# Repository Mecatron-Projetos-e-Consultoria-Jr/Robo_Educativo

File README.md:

# Robo_Educativo(Lembrar de tirar essa parte)

# Instalação
- Preparando a IDE: A IDE do Arduino não possui nativamente as placas da espressif em seu banco de dados. Portanto, é necessário instalar a ESP. [Este artigo](https://www.usinainfo.com.br/blog/programar-esp32-com-a-ide-arduino-tutorial-completo/) ensina passo a passo o processo(Configuração do ESP32 na IDE do Arduino). 
- Para que a interface funcione, copie a biblioteca do Nextion, localizada em Programação/IHM 3,5/Biblioteca_Nextion_ESP, para a basta "libraries" criada localmente pela IDE.
- O arquivo da programação principal está em Programação/ESP32/src/main.cpp. 
- Antes de realizar o upload para o microcontrolador no arquivo main.cpp é preciso mudar as configurações da conexão wifi. Nas linhas 15 e 16 mude para o nome e senha de rede local, respectivamente.
- Depois de tudo configurado, faça o upload da programação para a ESP32.

-------------------------------------------------------------------------------------------------------------------

# Robô Educativo

## Project Overview 
Desenvolvimento de uma interface hibrida que permite a integração e utilização de sensores de três diferentes kits robóticos de aprendizagem: Kazi EV5, Engino, Fischer Technik. Composto por 3 shields, e um centro de controle com uma tela touch para interação homem-máquina.

### Tecnologias utilizadas

#### Controle 

|Tipo|Nome|
|----|----|
|Sensor|`Fischer`|
|Sensor|`Engino`|
|Sensor|`Kazi`|
|Sensor|`Grove`|
|Comunicação|`OTA`|
|Linguagem|`C++`|

#### Eletrônica 

|Tipo|Nome|
|----|----|
|Controlador|`ESP32`|

#### Software

|Tipo|Nome|
|----|----|
|Interface|`Nextion Touch Screen`|

## Detalhes

### Datas
- Início - 020
- Fim - 021
### Membros Executores 
- Crotti (saiu na metade do projeto)- `ECA019`;
- Erik - `ECA019`;
- Natália - `ECA020`.

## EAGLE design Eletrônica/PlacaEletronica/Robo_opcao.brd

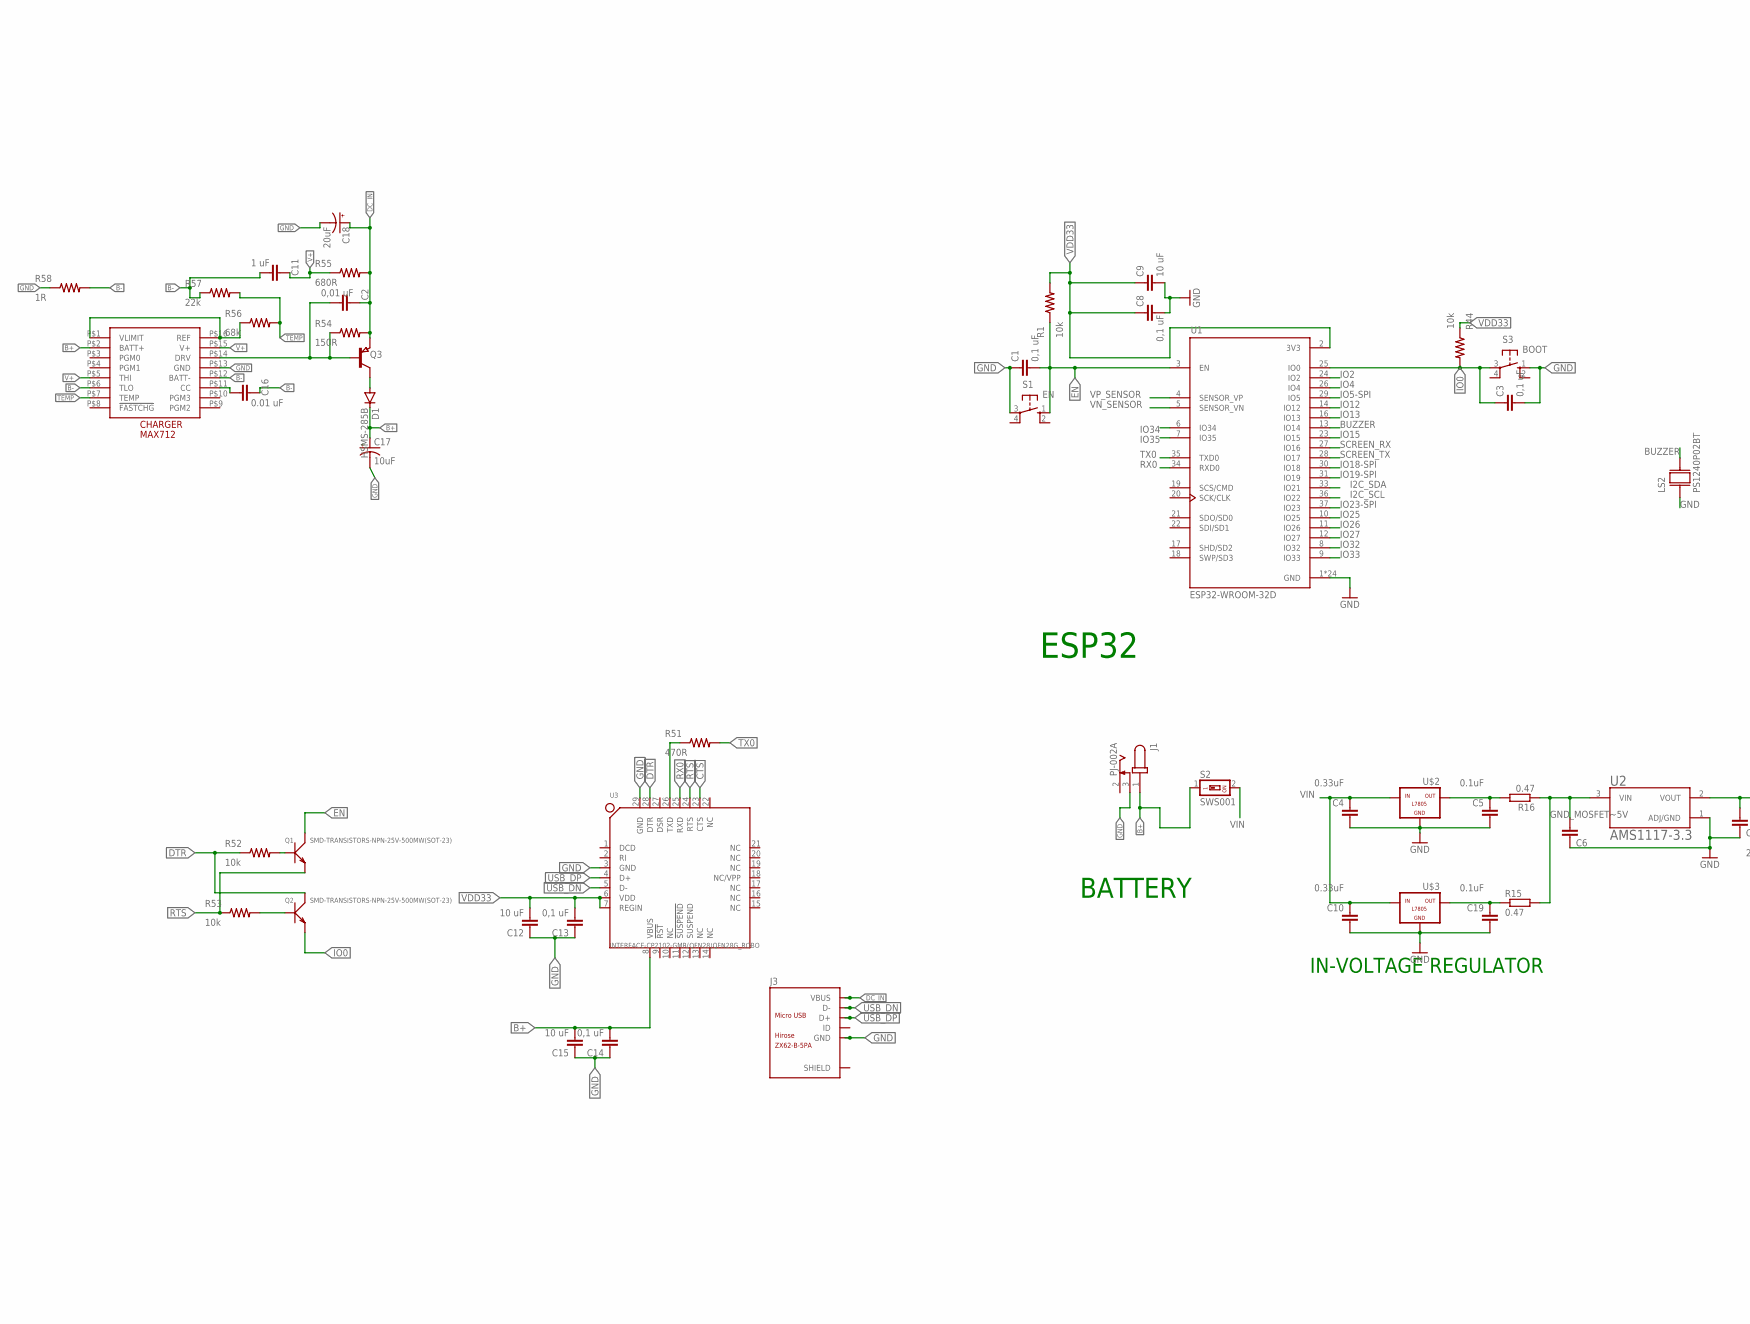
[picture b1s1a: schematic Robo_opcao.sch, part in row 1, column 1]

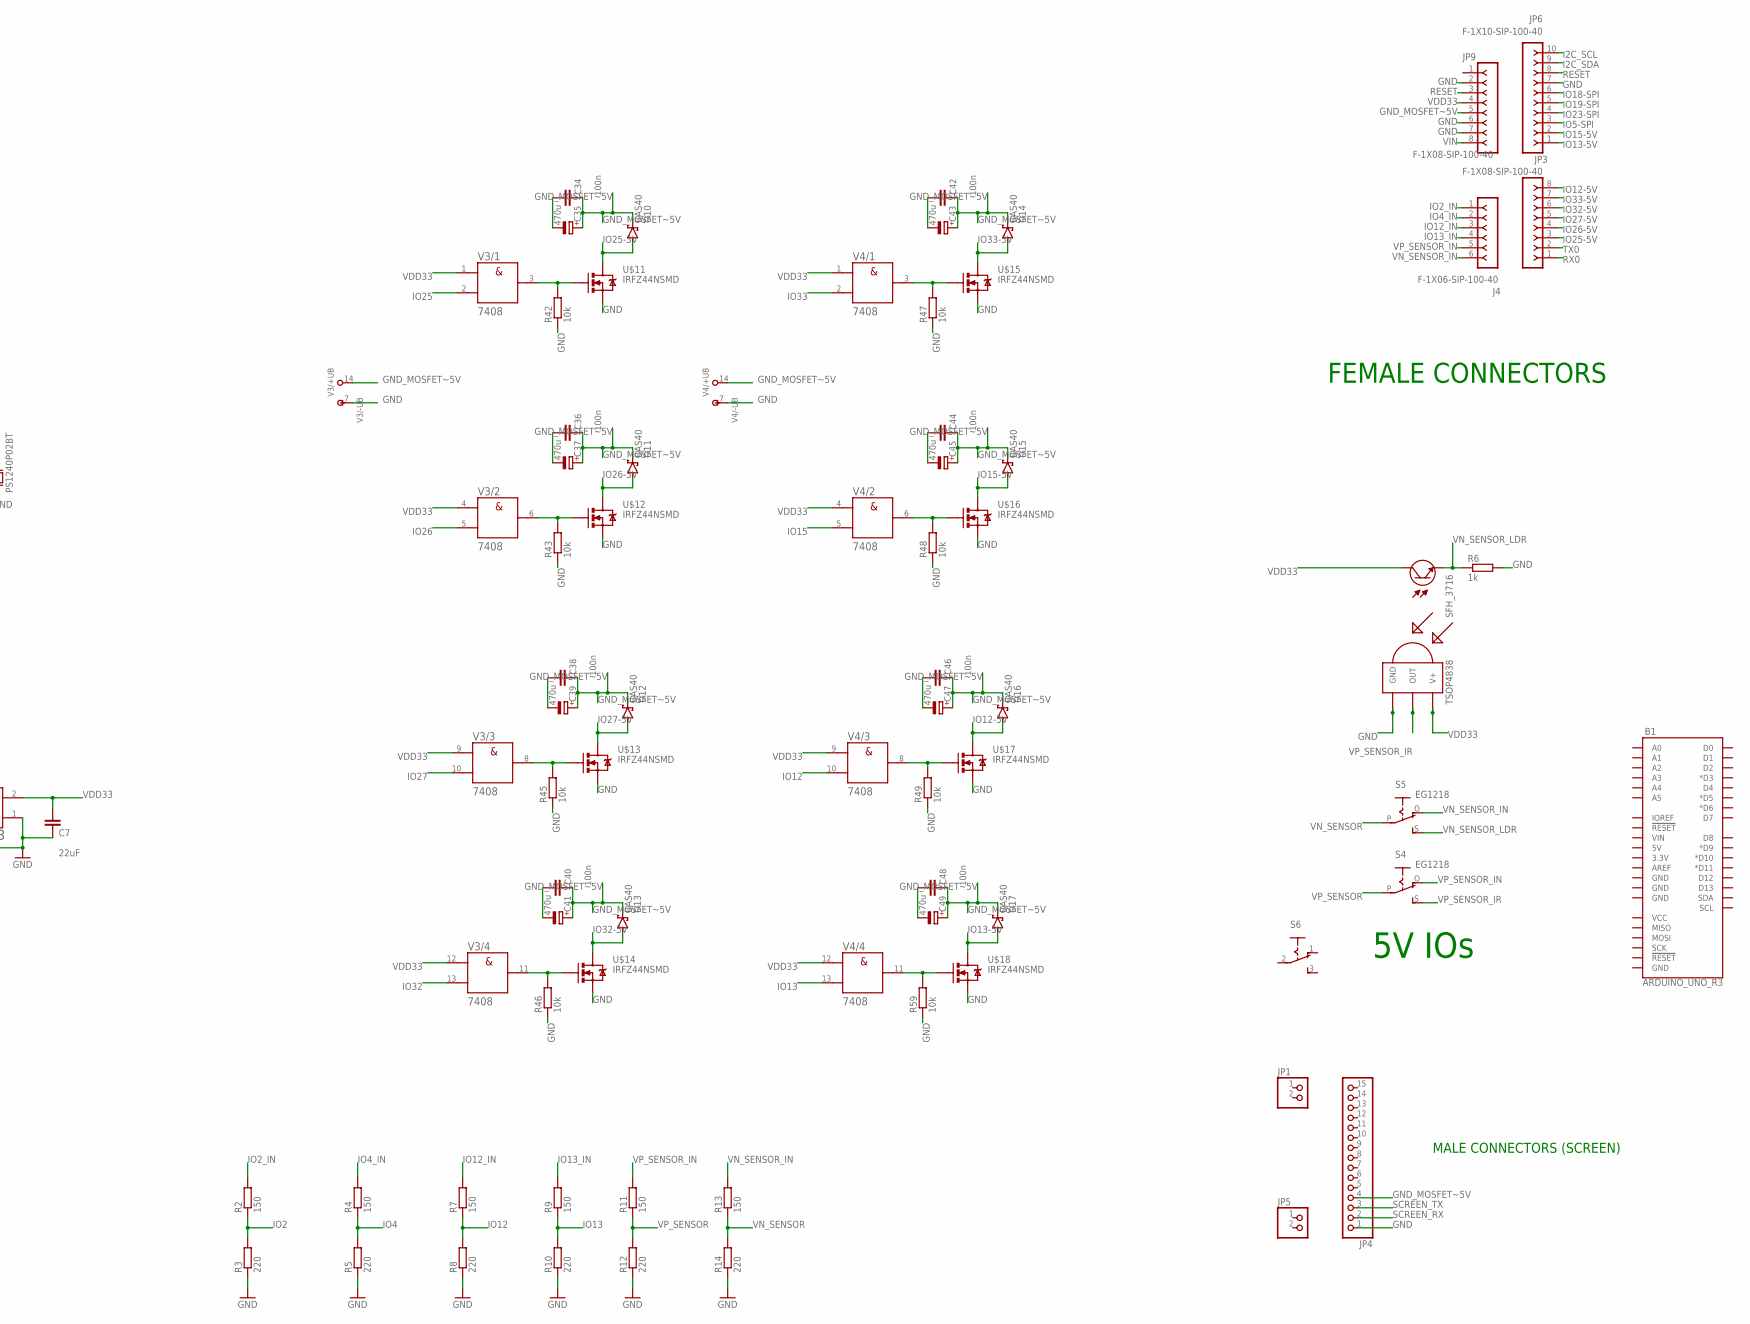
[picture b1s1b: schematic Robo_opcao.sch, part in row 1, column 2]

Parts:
B1: ARDUINO_UNO_R3; ARDUINO_R3
C1, C3, C8, C13, C14: 0,1 uF; C0603
C2: 0,01 uF; C0603
C4, C10: 0.33uF; 0402
C5, C6, C19: 0.1uF; 0402
C7: 22uF; 0402
C9, C12, C15: 10 uF; C0603
C11: 1 uF; C0603
C16: 0.01 uF; C0603
C17: 10uF; 0402_POL
C18: 20uF; 0402_POL
C34, C36, C38, C40, C42, C44, C46, C48: 100n; 0402
C35, C37, C39, C41, C43, C45, C47, C49: 470u; 150CLZ-0810
CHARGER: MAX712; DIP14
D1: HSMS-285B; SOT323
D10, D11, D12, D13, D14, D15, D16, D17: BAS40; SOT23
J1: PJ-002A; CUI_PJ-002A
J3: ZX62-B-5PA; ZX62-B-5PA(11)
J4: F-1X06-SIP-100-40; SIP-100-06-40
JP1, JP5: PINHD-1X2_2.54-SMD; 1X02SMD
JP3, JP9: F-1X08-SIP-100-40; SIP-100-08-40
JP4: PINHD-1X15_2.54-SMD; 1X15SMD
JP6: F-1X10-SIP-100-40; SIP-100-10-40
LS2: PS1240P02BT; XDCR_PS1240P02BT
Q1, Q2: SMD-TRANSISTORS-NPN-25V-500MW(SOT-23); SOT-23
Q3: PNP-TRANSISTOR_SOT23; SOT23
Q4: SFH_3716; TRANS_SFH_3716
Q5: TSOP4838; TSOP18XX
R1, R44, R52, R53: 10k; 0402
R2, R4, R7, R9, R11, R13: 150; M0805
R3, R5, R8, R10, R12, R14: 220; M0805
R6: 1k; M0805
R15, R16: 0.47; M0805
R42, R43, R45, R46, R47, R48, R49, R59: 10k; M0805
R51: 470R; 0402
R54: 150R; 0402
R55: 680R; 0402
R56: 68k; 0402
R57: 22k; 0402
R58: 1R; 0402
S1: EN; B3F-10XX
S2: SWS001; SMS-001
S3: BOOT; B3F-10XX
S4, S5: EG1218; EG1218_ROBO
S6: 255SB
U1: ESP32-WROOM-32D; MODULE_ESP32-WROOM-32D
U2: AMS1117-3.3; SOT229P700X180-4N
U3: INTERFACE-CP2102-GMR(QFN28)QFN28G_ROBO; QFN28G_0.5-5X5MM_ROBO
U$2, U$3: -L7805; L7805
U$11, U$12, U$13, U$14, U$15, U$16, U$17, U$18: IRFZ44NSMD; SMD
V3, V4: 7408; DIL14_FT

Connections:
B+: C14.2, C15.2, C17.P+ (+), CHARGER.P$2 (BATT+), D1.3 (C), J1.1, S2.1, U3.8 (VBUS)
B-: C11.2, C16.1, CHARGER.P$6 (TLO), CHARGER.P$12 (BATT-), R57.1, R58.2
BUZZER: LS2.2, U1.13 (IO14)
CTS: U3.23 (CTS)
DC_IN: C2.1, C18.P+ (+), J3.1 (VBUS), Q3.2 (E), R54.2, R55.2
DTR: Q2.3 (C), R52.1, U3.28 (DTR)
EN: C1.2, Q1.3 (C), R1.1, S1.1 (S), U1.3 (EN)
GND: C1.1, C3.2, C4.1, C5.1, C6.2, C7.2, C8.2, C9.2, C10.1, C12.1, C13.1, C14.1, C15.1, C17.P- (-), C18.P- (-), C19.1, CHARGER.P$13 (GND), J1.3, J3.5 (GND), JP4.1, JP6.7, JP9.2, JP9.6, JP9.7, LS2.1, Q5.GND, R3.1, R5.1, R6.2, R8.1, R10.1, R12.1, R14.1, R42.1, R43.1, R45.1, R46.1, R47.1, R48.1, R49.1, R58.1, R59.1, S1.3, S3.1 (S), U1.1 (GND), U1.15 (GND), U1.38 (GND), U1.39_1 (GND), U1.39_2 (GND), U1.39_3 (GND), U1.39_4 (GND), U1.39_5 (GND), U1.39_6 (GND), U1.39_7 (GND), U1.39_8 (GND), U1.39_9 (GND), U1.39_10 (GND), U1.39_11 (GND), U1.39_12 (GND), U1.39_13 (GND), U1.39_14 (GND), U1.39_15 (GND), U1.39_16 (GND), U1.39_17 (GND), U1.39_18 (GND), U1.39_19 (GND), U1.39_20 (GND), U1.39_21 (GND), U2.1 (ADJ/GND), U3.3 (GND), U3.29 (GND), U$2.GND, U$3.GND, U$11.3 (S), U$12.3 (S), U$13.3 (S), U$14.3 (S), U$15.3 (S), U$16.3 (S), U$17.3 (S), U$18.3 (S), V3.7 (-UB), V4.7 (-UB)
GND_MOSFET~5V: C6.1, C34.2, C35.+, C36.2, C37.+, C38.2, C39.+, C40.2, C41.+, C42.2, C43.+, C44.2, C45.+, C46.2, C47.+, C48.2, C49.+, D10.3 (C), D11.3 (C), D12.3 (C), D13.3 (C), D14.3 (C), D15.3 (C), D16.3 (C), D17.3 (C), JP4.4, JP9.5, R15.2, R16.1, U2.3 (VIN), V3.14 (+UB), V4.14 (+UB)
I2C_SCL: JP6.10, U1.36 (IO22)
I2C_SDA: JP6.9, U1.33 (IO21)
IO0: C3.1, Q2.2 (E), R44.2, S3.3, U1.25 (IO0)
IO2: R2.1, R3.2, U1.24 (IO2)
IO2_IN: J4.1, R2.2
IO4: R4.1, R5.2, U1.26 (IO4)
IO4_IN: J4.2, R4.2
IO5-SPI: JP6.3, U1.29 (IO5)
IO12: R7.1, R8.2, U1.14 (IO12), V4.10 (B)
IO12-5V: D16.1 (A), JP3.8, U$17.2 (D)
IO12_IN: J4.3, R7.2
IO13: R9.1, R10.2, U1.16 (IO13), V4.13 (B)
IO13-5V: D17.1 (A), JP6.1, U$18.2 (D)
IO13_IN: J4.4, R9.2
IO15: U1.23 (IO15), V4.5 (B)
IO15-5V: D15.1 (A), JP6.2, U$16.2 (D)
IO18-SPI: JP6.6, U1.30 (IO18)
IO19-SPI: JP6.5, U1.31 (IO19)
IO23-SPI: JP6.4, U1.37 (IO23)
IO25: U1.10 (IO25), V3.2 (B)
IO25-5V: D10.1 (A), JP3.3, U$11.2 (D)
IO26: U1.11 (IO26), V3.5 (B)
IO26-5V: D11.1 (A), JP3.4, U$12.2 (D)
IO27: U1.12 (IO27), V3.10 (B)
IO27-5V: D12.1 (A), JP3.5, U$13.2 (D)
IO32: U1.8 (IO32), V3.13 (B)
IO32-5V: D13.1 (A), JP3.6, U$14.2 (D)
IO33: U1.9 (IO33), V4.2 (B)
IO33-5V: D14.1 (A), JP3.7, U$15.2 (D)
IO34: U1.6 (IO34)
IO35: U1.7 (IO35)
unnamed: C19.2, R15.1, U$3.OUT
unnamed: C5.2, R16.2, U$2.OUT
unnamed: R51.1, U3.26 (TXD)
unnamed: C34.1, C35.-
unnamed: C36.1, C37.-
unnamed: Q1.1 (B), R52.2
unnamed: C38.1, C39.-
unnamed: C40.1, C41.-
unnamed: C42.1, C43.-
unnamed: C44.1, C45.-
unnamed: C46.1, C47.-
unnamed: C48.1, C49.-
unnamed: Q2.1 (B), R53.2
unnamed: C2.2, CHARGER.P$14 (DRV), Q3.1 (B), R54.1
unnamed: R42.2, U$11.1 (G), V3.3 (Y)
unnamed: D1.1 (A), Q3.3 (C)
unnamed: C16.2, CHARGER.P$11 (CC)
unnamed: CHARGER.P$1 (VLIMIT), CHARGER.P$16 (REF), R56.1
unnamed: R43.2, U$12.1 (G), V3.6 (Y)
unnamed: R45.2, U$13.1 (G), V3.8 (Y)
unnamed: R46.2, U$14.1 (G), V3.11 (Y)
unnamed: R47.2, U$15.1 (G), V4.3 (Y)
unnamed: R48.2, U$16.1 (G), V4.6 (Y)
unnamed: R49.2, U$17.1 (G), V4.8 (Y)
unnamed: R59.2, U$18.1 (G), V4.11 (Y)
RESET: JP6.8, JP9.3
RTS: Q1.2 (E), R53.1, U3.24 (RTS)
RX0: JP3.1, U1.34 (RXD0), U3.25 (RXD)
SCREEN_RX: JP4.2, U1.27 (IO16)
SCREEN_TX: JP4.3, U1.28 (IO17)
TEMP: CHARGER.P$7 (TEMP), R56.2, R57.2
TX0: JP3.2, R51.2, U1.35 (TXD0)
USB_DN: J3.2 (D-), U3.5 (D-)
USB_DP: J3.3 (D+), U3.4 (D+)
V+: C11.1, CHARGER.P$5 (THI), CHARGER.P$15 (V+), R55.1
VDD33: C7.1, C8.1, C9.1, C12.2, C13.2, JP9.4, Q4.1 (C), Q5.VCC (V+), R1.2, R44.1, U1.2 (3V3), U2.2 (VOUT), U3.6 (VDD), U3.7 (REGIN), V3.1 (A), V3.4 (A), V3.9 (A), V3.12 (A), V4.1 (A), V4.4 (A), V4.9 (A), V4.12 (A)
VIN: C4.2, C10.2, JP9.8, S2.2, U$2.IN, U$3.IN
VN_SENSOR: R13.1, R14.2, S5.P, U1.5 (SENSOR_VN)
VN_SENSOR_IN: J4.6, R13.2, S5.O
VN_SENSOR_LDR: Q4.2 (E), R6.1, S5.S
VP_SENSOR: R11.1, R12.2, S4.P, U1.4 (SENSOR_VP)
VP_SENSOR_IN: J4.5, R11.2, S4.O
VP_SENSOR_IR: Q5.OUT, S4.S

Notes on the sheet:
IN-VOLTAGE REGULATOR
FEMALE CONNECTORS
MALE CONNECTORS (SCREEN)
BATTERY
5V IOs
ESP32

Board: 2 copper layers, 116 parts (40 on the bottom side), 80 nets, no tracks yet.

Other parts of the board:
U$1: NEXTION

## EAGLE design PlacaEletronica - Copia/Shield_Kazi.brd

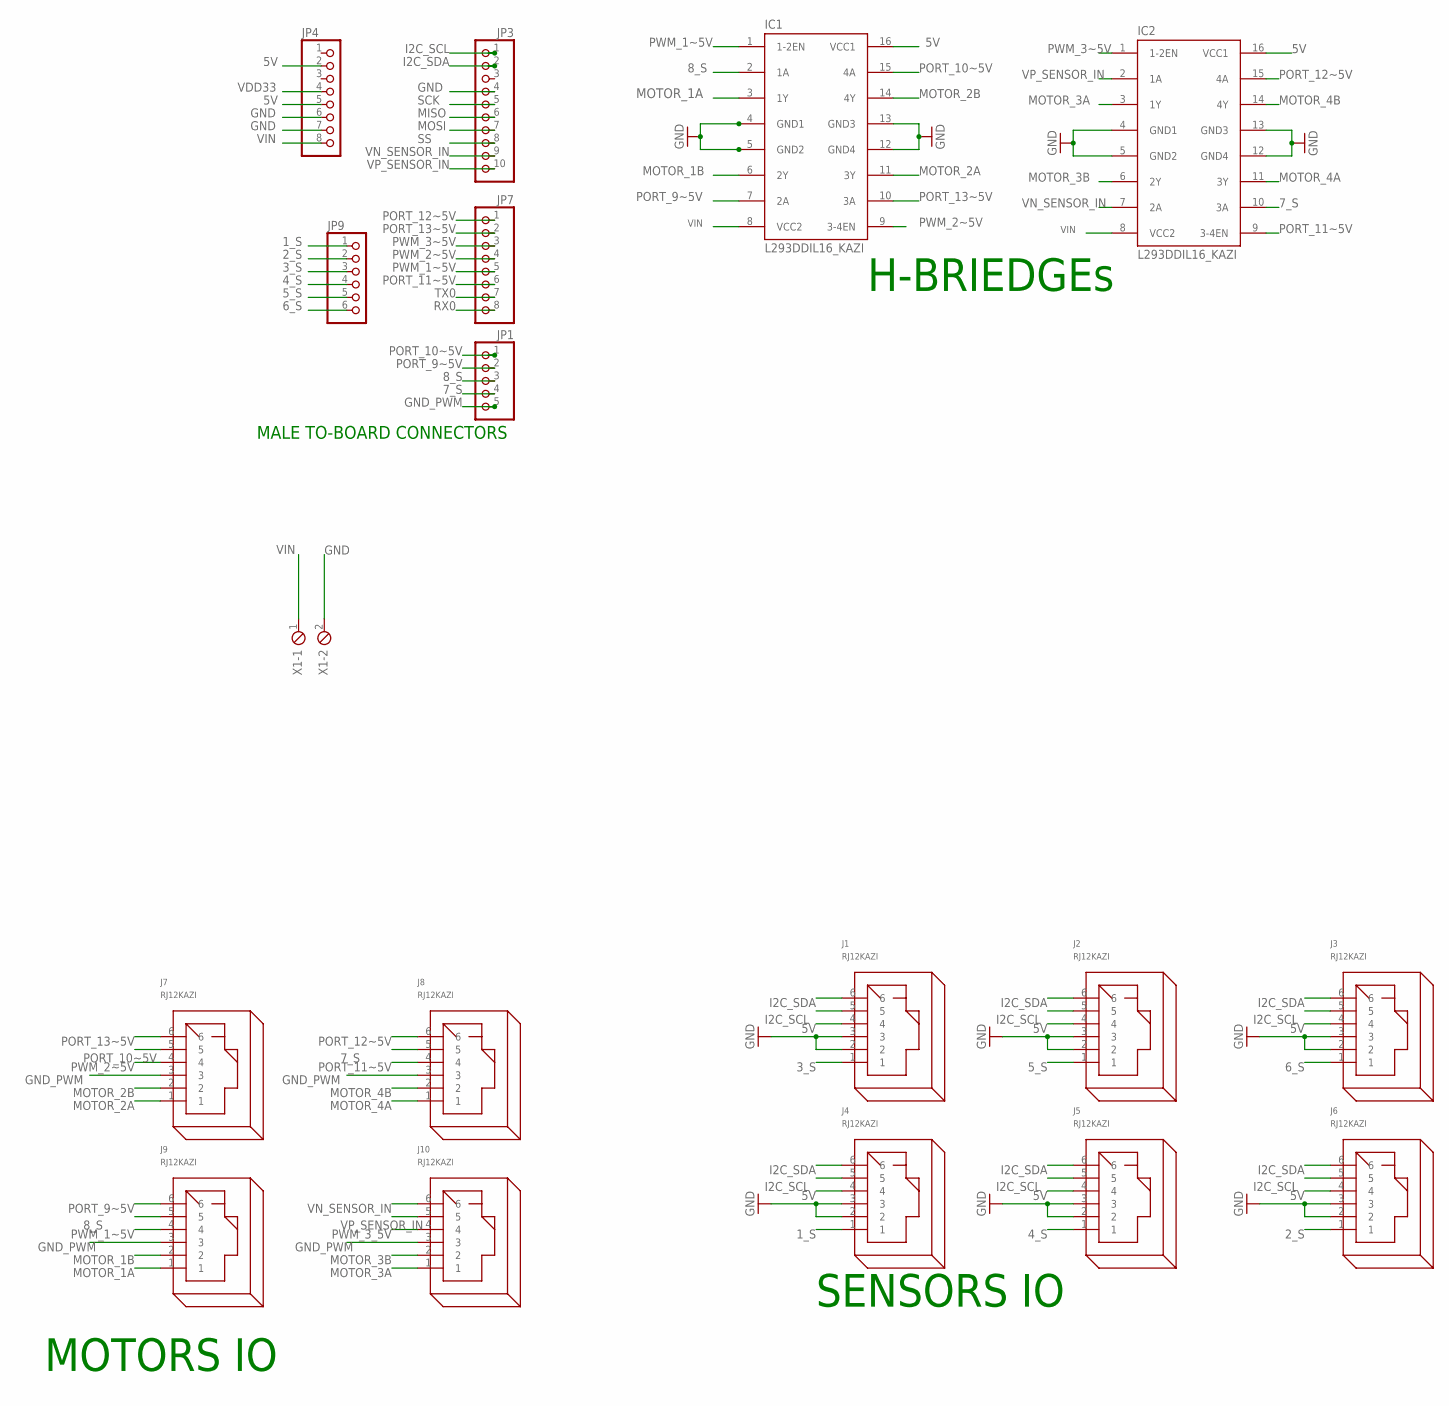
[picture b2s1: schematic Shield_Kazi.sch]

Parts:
IC1, IC2: L293DDIL16_KAZI; DIL16_KAZI
J1, J2, J3, J4, J5, J6, J7, J8, J9, J10: RJ12KAZI; RJ12_KAZI
JP1: PINHD-1X5_2.54-SMD; 1X05SMD
JP3: PINHD-1X10_2.54-SMD; 1X10SMD
JP4, JP7: PINHD-1X8_2.54-SMD; 1X08SMD
JP9: PINHD-1X6_2.54-SMD; 1X06SMD
X1: MPT21.3; 2POL254_1.3

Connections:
1_S: J4.1, JP9.1
2_S: J6.1, JP9.2
3_S: J1.1, JP9.3
4_S: J5.1, JP9.4
5V: IC1.16 (VCC1), IC2.16 (VCC1), J1.4, J2.4, J3.4, J4.4, J5.4, J6.4, JP4.2, JP4.5
5_S: J2.1, JP9.5
6_S: J3.1, JP9.6
7_S: IC2.10 (3A), J8.5, JP1.4
8_S: IC1.2 (1A), J9.5, JP1.3
GND: IC1.4 (GND1), IC1.5 (GND2), IC1.12 (GND4), IC1.13 (GND3), IC2.4 (GND1), IC2.5 (GND2), IC2.12 (GND4), IC2.13 (GND3), J1.2, J1.3, J2.2, J2.3, J3.2, J3.3, J4.2, J4.3, J5.2, J5.3, J6.2, J6.3, JP3.4, JP4.6, JP4.7, X1.2
GND_PWM: J7.3, J8.3, J9.3, J10.3, JP1.5
I2C_SCL: J1.5, J2.5, J3.5, J4.5, J5.5, J6.5, JP3.1
I2C_SDA: J1.6, J2.6, J3.6, J4.6, J5.6, J6.6, JP3.2
MISO: JP3.6
MOSI: JP3.7
MOTOR_1A: IC1.3 (1Y), J9.1
MOTOR_1B: IC1.6 (2Y), J9.2
MOTOR_2A: IC1.11 (3Y), J7.1
MOTOR_2B: IC1.14 (4Y), J7.2
MOTOR_3A: IC2.3 (1Y), J10.1
MOTOR_3B: IC2.6 (2Y), J10.2
MOTOR_4A: IC2.11 (3Y), J8.1
MOTOR_4B: IC2.14 (4Y), J8.2
PORT_9~5V: IC1.7 (2A), J9.6, JP1.2
PORT_10~5V: IC1.15 (4A), J7.5, JP1.1
PORT_11~5V: IC2.9 (3-4EN), J8.4, JP7.6
PORT_12~5V: IC2.15 (4A), J8.6, JP7.1
PORT_13~5V: IC1.10 (3A), J7.6, JP7.2
PWM_1~5V: IC1.1 (1-2EN), J9.4, JP7.5
PWM_2~5V: IC1.9 (3-4EN), J7.4, JP7.4
PWM_3_5V: J10.4
PWM_3~5V: IC2.1 (1-2EN), JP7.3
RX0: JP7.8
SCK: JP3.5
SS: JP3.8
TX0: JP7.7
VDD33: JP4.4
VIN: IC1.8 (VCC2), IC2.8 (VCC2), JP4.8, X1.1
VN_SENSOR_IN: IC2.7 (2A), J10.6, JP3.9
VP_SENSOR_IN: IC2.2 (1A), J10.5, JP3.10

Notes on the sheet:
MALE TO-BOARD CONNECTORS
H-BRIEDGEs
SENSORS IO
MOTORS IO

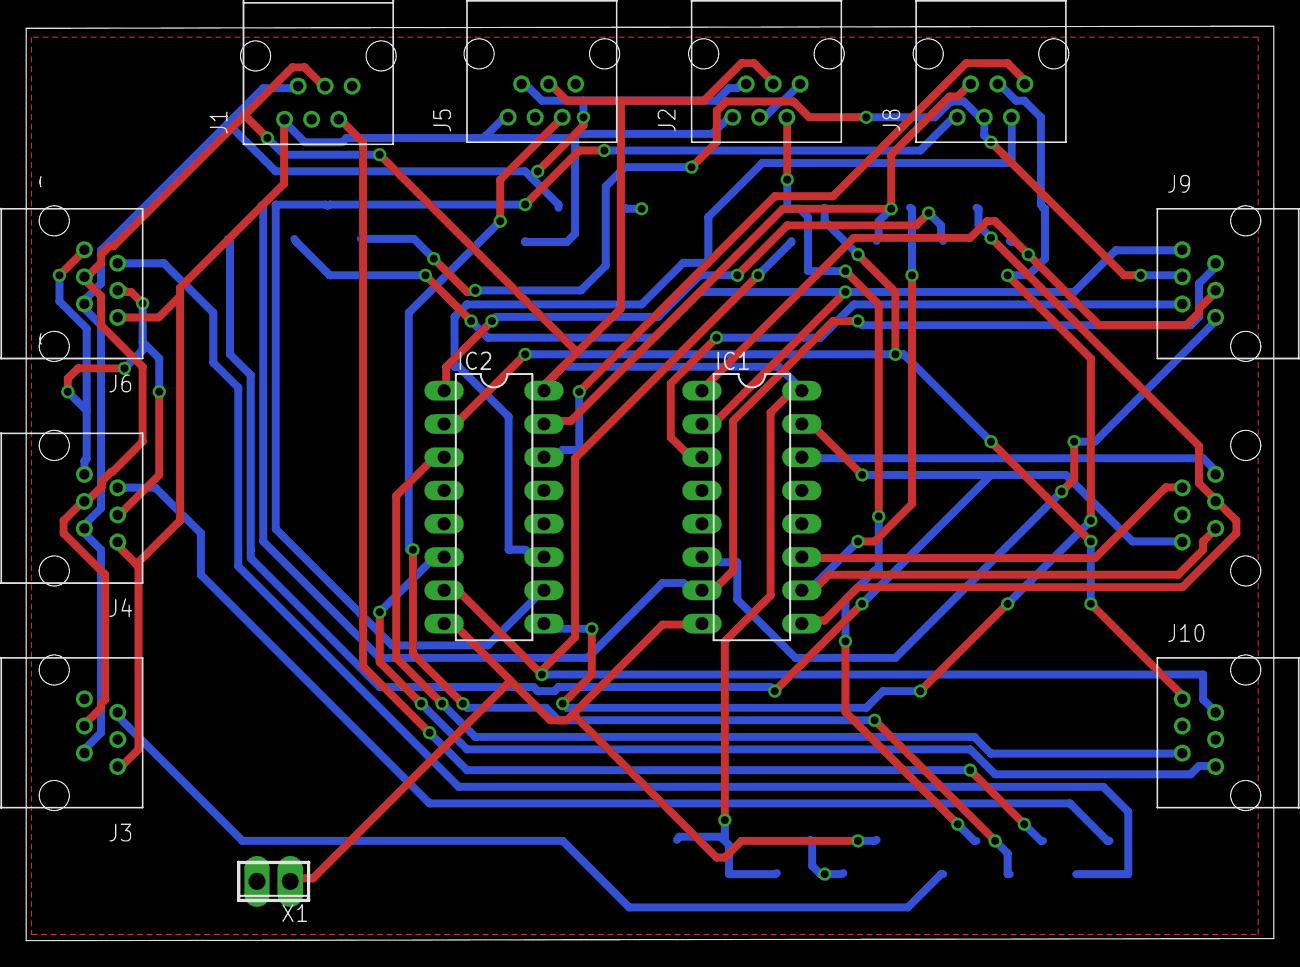
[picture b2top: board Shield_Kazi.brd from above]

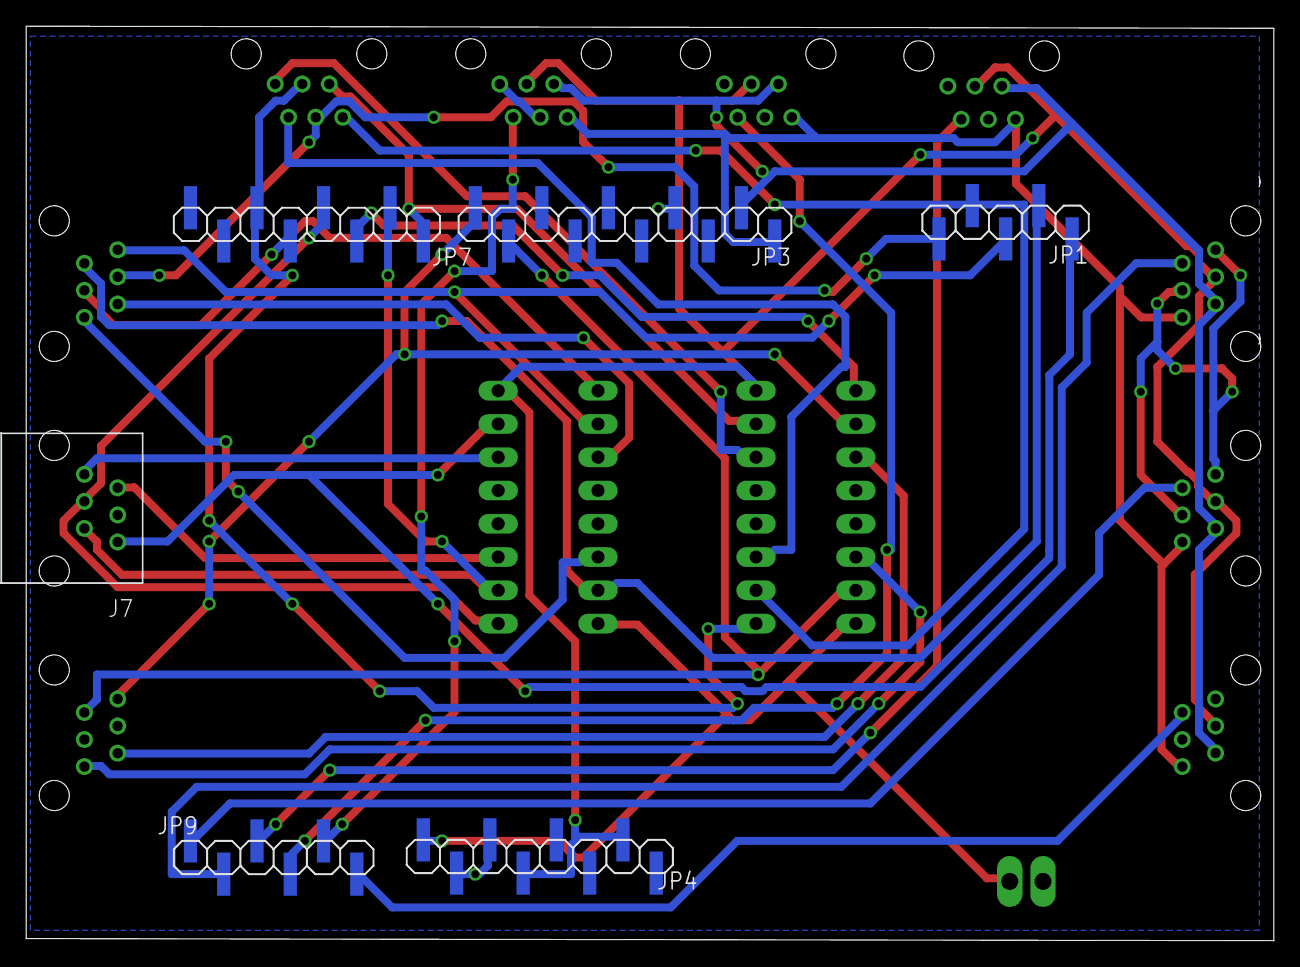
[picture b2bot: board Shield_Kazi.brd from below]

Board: 2 copper layers, 95.2 x 69.8 mm, 18 parts (6 on the bottom side), 32 nets.

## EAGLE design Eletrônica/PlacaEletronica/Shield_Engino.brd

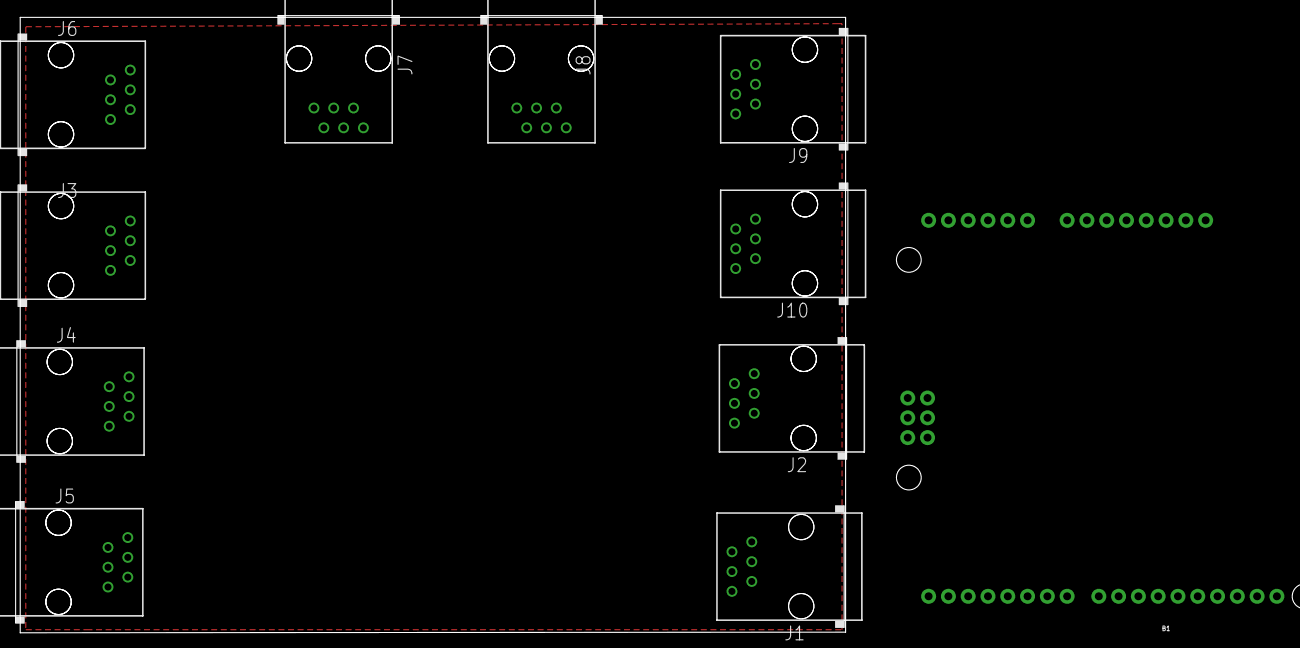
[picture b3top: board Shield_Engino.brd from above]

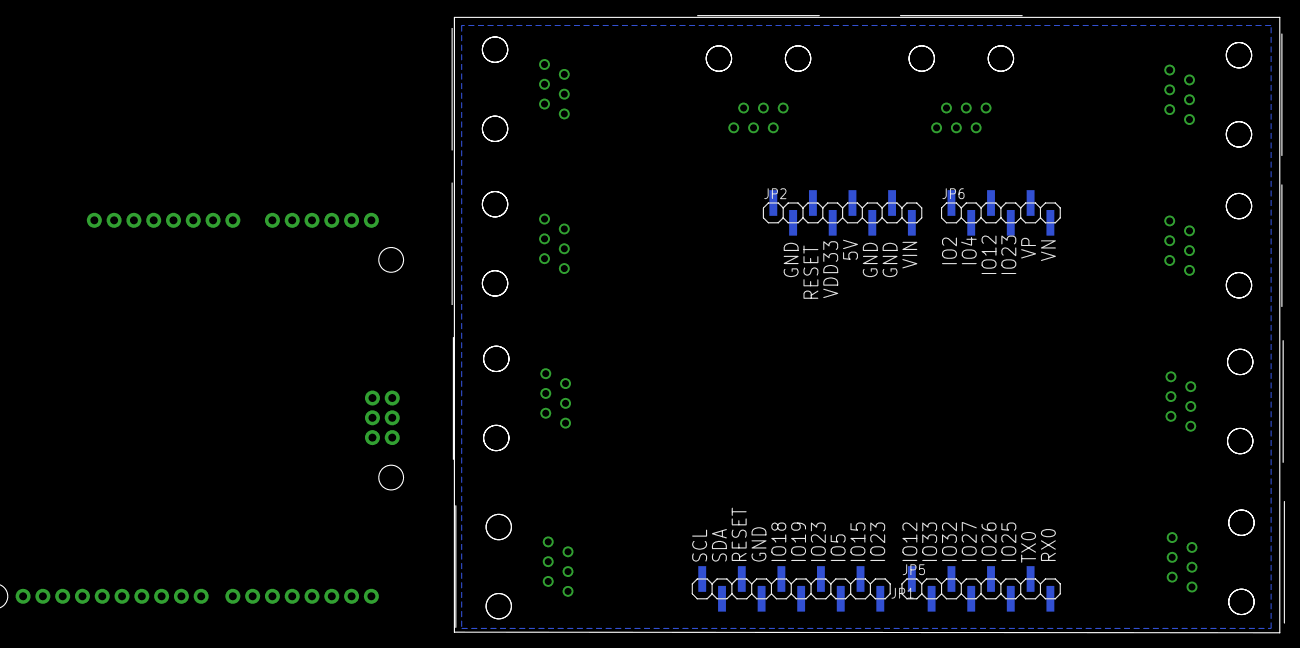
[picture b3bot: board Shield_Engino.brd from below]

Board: 2 copper layers, 106.8 x 79.2 mm, 15 parts (4 on the bottom side), 21 nets, no tracks yet.

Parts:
B1: ARDUINO_UNO_R3; ARDUINO_R3
J1, J2, J3, J4, J5, J6, J7, J8, J9, J10: RJ11-2L-B; RJ11-NO_SHIELD
JP1: 1X10SMD
JP2, JP5: 1X08SMD
JP6: 1X06SMD

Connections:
5V: J1.4, J1.5, J2.4, J2.5, J3.5, J4.5, J5.5, J6.5, J7.5, J8.4, J8.5, J9.4, J9.5, J10.4, J10.5, JP2.5
GND: J3.4, J4.4, J5.4, J6.4, J7.4, JP1.7, JP2.2, JP2.6, JP2.7
I2C_SCL~5V: J3.3, J4.3, J5.3, J6.3, J7.3, JP1.10
I2C_SDA~5V: J3.1, J4.1, J5.1, J6.1, J7.1, JP1.9
IO2: J3.2, JP6.1
IO4: J4.2, JP6.2
IO5: J7.6, JP1.3
IO12: J2.6, J5.2, JP5.1, JP6.3
IO15: J4.6, JP1.2
IO19: J9.2, JP1.5
IO23: J3.6, J6.2, J8.2, JP1.1, JP1.4, JP6.4
IO25: J1.2, JP5.6
IO26: J1.6, JP5.5
IO27: J9.6, JP5.4
IO32: J8.6, JP5.3
IO33: J10.6, JP5.2
RESET: JP1.8, JP2.3
RX0: J10.2, JP5.8
TX0: J2.2, JP5.7
VN_SENSOR_IN: J6.6, JP6.6
VP_SENSOR_IN: J5.6, J7.2, JP6.5

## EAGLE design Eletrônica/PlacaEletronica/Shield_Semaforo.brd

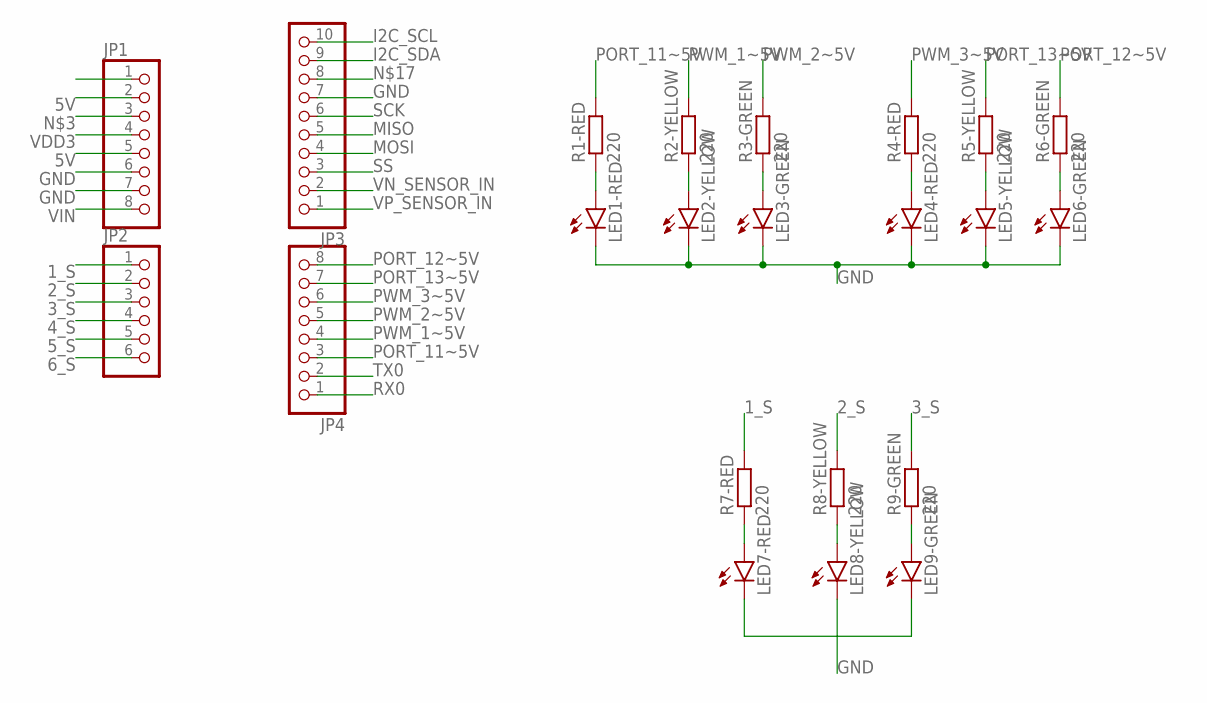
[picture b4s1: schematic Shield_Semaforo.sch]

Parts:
JP1, JP4: PINHD-1X8_2.54-SMD; 1X08SMD
JP2: PINHD-1X6_2.54-SMD; 1X06SMD
JP3: PINHD-1X10_2.54-SMD; 1X10SMD
LED1-RED, LED2-YELLOW, LED3-GREEN, LED4-RED, LED5-YELLOW, LED6-GREEN, LED7-RED, LED8-YELLOW, LED9-GREEN: LED5MM
R1-RED, R2-YELLOW, R3-GREEN, R4-RED, R5-YELLOW, R6-GREEN, R7-RED, R8-YELLOW, R9-GREEN: 220; M0805

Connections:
1_S: JP2.1, R7-RED.2
2_S: JP2.2, R8-YELLOW.2
3_S: JP2.3, R9-GREEN.2
4_S: JP2.4
5V: JP1.2, JP1.5
5_S: JP2.5
6_S: JP2.6
GND: JP1.6, JP1.7, JP3.7, LED1-RED.K (C), LED2-YELLOW.K (C), LED3-GREEN.K (C), LED4-RED.K (C), LED5-YELLOW.K (C), LED6-GREEN.K (C), LED8-YELLOW.K (C)
I2C_SCL: JP3.10
I2C_SDA: JP3.9
MISO: JP3.5
MOSI: JP3.4
unnamed: LED1-RED.A, R1-RED.1
unnamed: LED2-YELLOW.A, R2-YELLOW.1
unnamed: LED3-GREEN.A, R3-GREEN.1
unnamed: LED4-RED.A, R4-RED.1
unnamed: LED5-YELLOW.A, R5-YELLOW.1
unnamed: LED6-GREEN.A, R6-GREEN.1
unnamed: LED7-RED.A, R7-RED.1
unnamed: LED8-YELLOW.A, R8-YELLOW.1
unnamed: LED9-GREEN.A, R9-GREEN.1
unnamed: LED7-RED.K (C), LED9-GREEN.K (C)
PORT_11~5V: JP4.3, R1-RED.2
PORT_12~5V: JP4.8, R6-GREEN.2
PORT_13~5V: JP4.7, R5-YELLOW.2
PWM_1~5V: JP4.4, R2-YELLOW.2
PWM_2~5V: JP4.5, R3-GREEN.2
PWM_3~5V: JP4.6, R4-RED.2
RX0: JP4.1
SCK: JP3.6
SS: JP3.3
TX0: JP4.2
VDD3: JP1.4
VIN: JP1.8
VN_SENSOR_IN: JP3.2
VP_SENSOR_IN: JP3.1

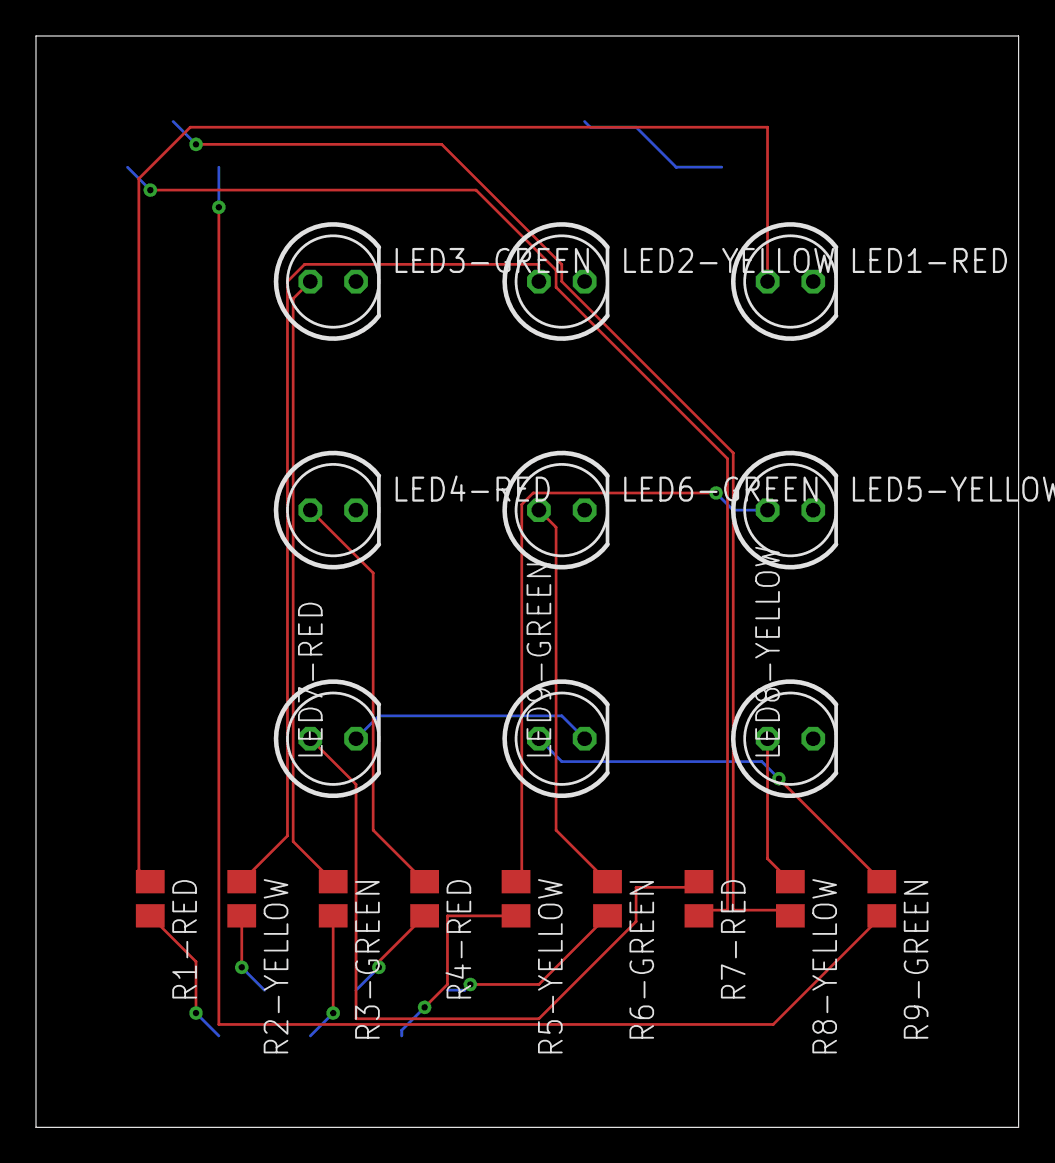
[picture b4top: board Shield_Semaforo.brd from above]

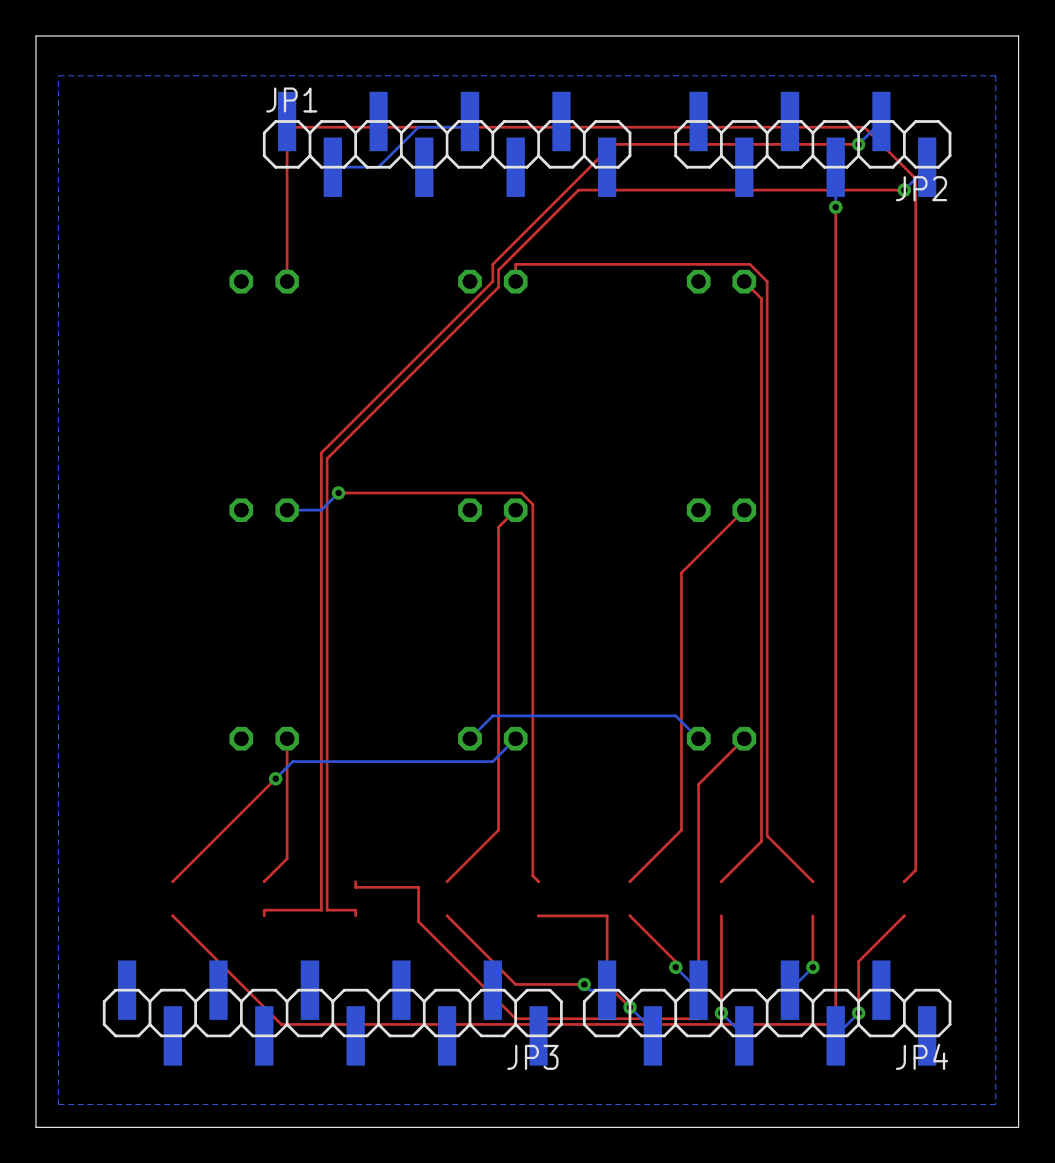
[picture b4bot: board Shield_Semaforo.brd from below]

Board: 2 copper layers, 54.6 x 60.6 mm, 22 parts (4 on the bottom side), 21 nets.

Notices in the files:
parts and their libraries:
con-headers-jp: Copyright (C) 2008, Bob Starr
SparkFun-Boards: Licensing: Creative Commons ShareAlike 4.0 International - https://creativecommons.org/licenses/by-sa/4.0
